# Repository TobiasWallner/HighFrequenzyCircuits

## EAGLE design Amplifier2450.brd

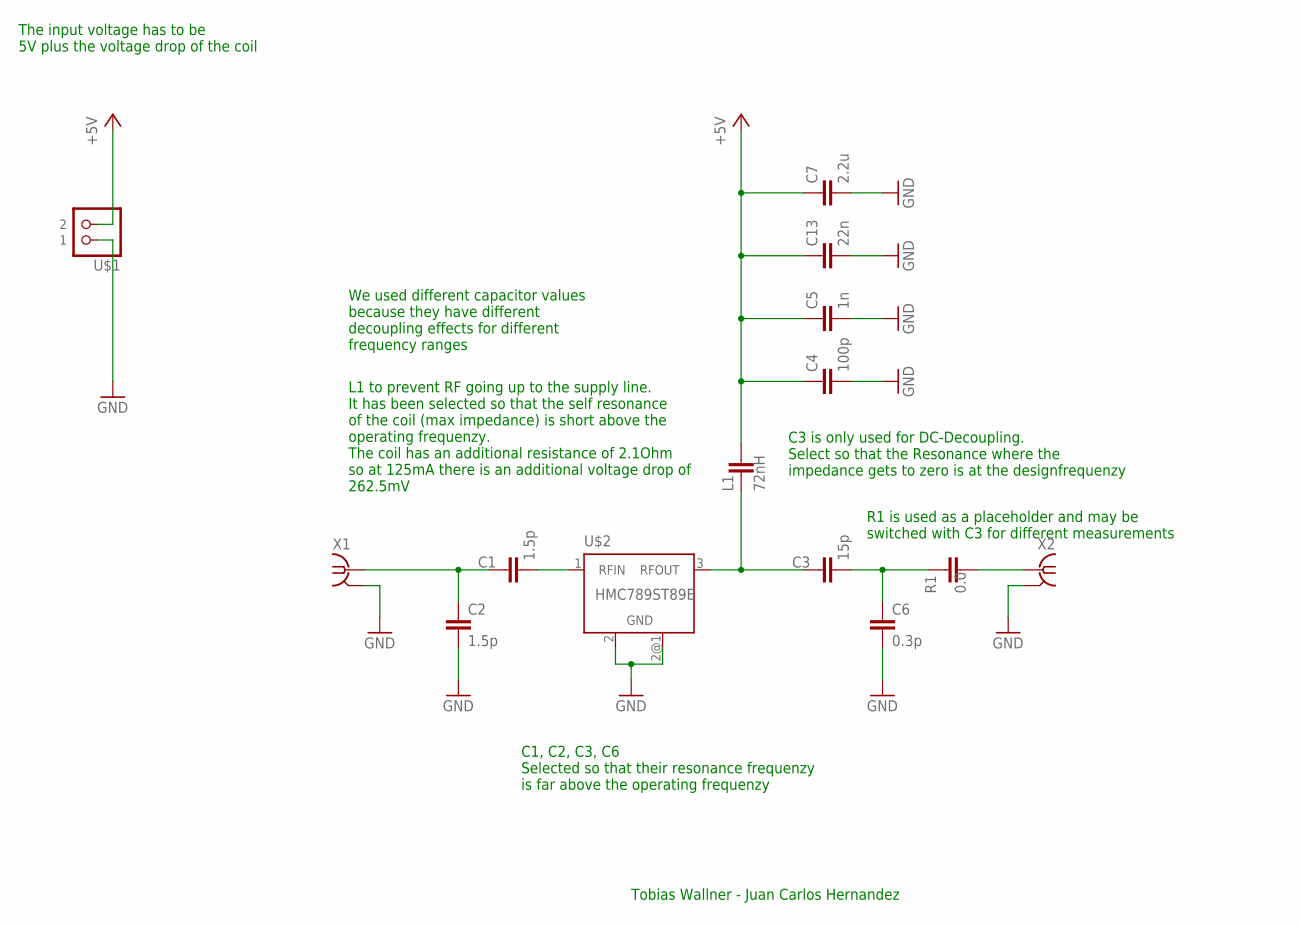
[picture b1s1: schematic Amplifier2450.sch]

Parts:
C1, C2: 1.5p; C0603
C3: 15p; C0603
C4: 100p; C0603
C5: 1n; C0603
C6: 0.3p; C0603
C7: 2.2u; C0805
C13: 22n; C0603
L1: 72nH; C0603
R1: 0.0; C0603
U$1: SKB_1X02_RM_5.12; RM_5.12_1X02
U$2: HMC789ST89E; SOT89
X1, X2: SMA-142-0701-801/806; J502-ND-142-0701-801/806

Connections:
+5V: C4.1, C5.1, C7.1, C13.1, L1.1, U$1.P$2 (2)
GND: C2.2, C4.2, C5.2, C6.2, C7.2, C13.2, U$1.P$1 (1), U$2.2 (GND), U$2.2@1 (GND), X1.G@1 (2), X1.G@2 (2), X1.G@3 (2), X1.G@4 (2), X2.G@1 (2), X2.G@2 (2), X2.G@3 (2), X2.G@4 (2)
unnamed: C3.1, L1.2, U$2.3 (RFOUT)
unnamed: C1.1, C2.1, X1.1
unnamed: C1.2, U$2.1 (RFIN)
unnamed: C3.2, C6.1, R1.1
unnamed: R1.2, X2.1

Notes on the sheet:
R1 is used as a placeholder and may be switched with C3 for different measurements
We used different capacitor values because they have different decoupling effects for different frequency ranges
Tobias Wallner - Juan Carlos Hernandez
C3 is only used for DC-Decoupling. Select so that the Resonance where the impedance gets to zero is at the designfrequenzy
C1, C2, C3, C6 Selected so that their resonance frequenzy is far above the operating frequenzy
L1 to prevent RF going up to the supply line. It has been selected so that the self resonance of the coil (max impedance) is short above the operating frequenzy. The coil has an additional resistance of 2.1Ohm so at 125mA there is an additional voltage drop of 262.5mV
The input voltage has to be 5V plus the voltage drop of the coil

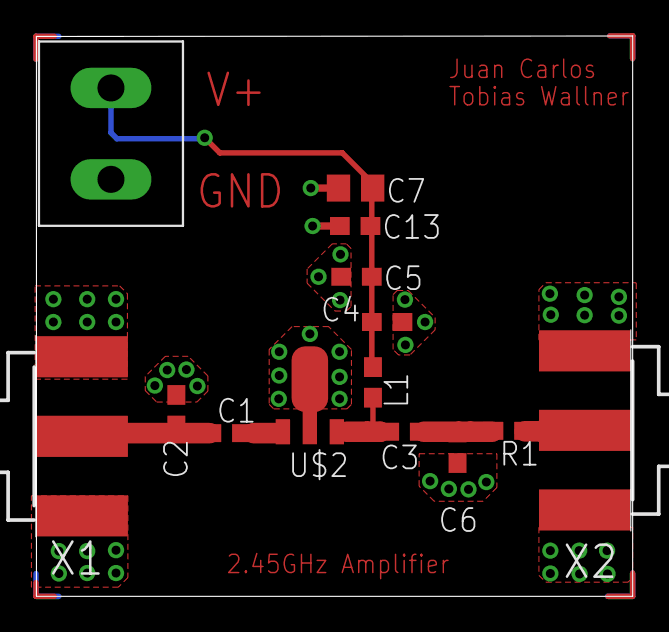
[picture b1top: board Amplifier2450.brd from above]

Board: 2 copper layers, 33.1 x 31.1 mm, 14 parts (0 on the bottom side), 7 nets.

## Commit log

2022-03-22 (tobias): added cool stuff
2022-03-22 (juanka): hey
2022-03-22 (tobias): added more cool stuff
2022-03-22 (Juanka): Added Barça in cool stuff
2022-03-22 (tobias): changes applied
2022-03-24 (JuanCarlos): First Schematic of Amp
2022-03-24 (Tobias): created Datasheets folder and added Some
2022-03-24 (Tobias): selected components and started the layout
2022-03-28 (Tobias): added datasheets
2022-03-28 (Tobias): Added Datasheet
2022-03-28 Finished the PCB design with the following ideas: Cutouts around the signal line to minimize the dielectric losses in the pcb material as well as the coating. cutout to seperate the noisy connector p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
2022-03-28 (Tobias):Added a suitable Zener Diode
2022-03-28 (Tobias): added a top layer ground plane cutout around the signal line to prevent spilling.
2022-03-28 (Tobias): extended the documentation about the coutout clearence
2022-03-28 (Tobias): extended the ordering with a Zener Diode RS-Components link
2022-03-29 (Tobias): started to apply changes from robert 1st meeting
2022-03-31 (Tobias): halfway applied Roberts feedback
2022-04-01 (Juanka): Updated PCB
2022-04-01 (Tobias): added documentation to the current design, explaining why certain parts and decisions have been made
2022-04-01 (Tobias): removed unnecessary parts from the ordering list that are no longer used in the new design
2022-04-01 (Tobias): fixed an error in the microstrip line plot. one datapoint of the permitivity was missing
2022-04-04 (Tobias): made finishing touches to the design
2022-04-04 (Tobias): fixed a typo
2022-04-05 (Tobias): changed the ordering list
